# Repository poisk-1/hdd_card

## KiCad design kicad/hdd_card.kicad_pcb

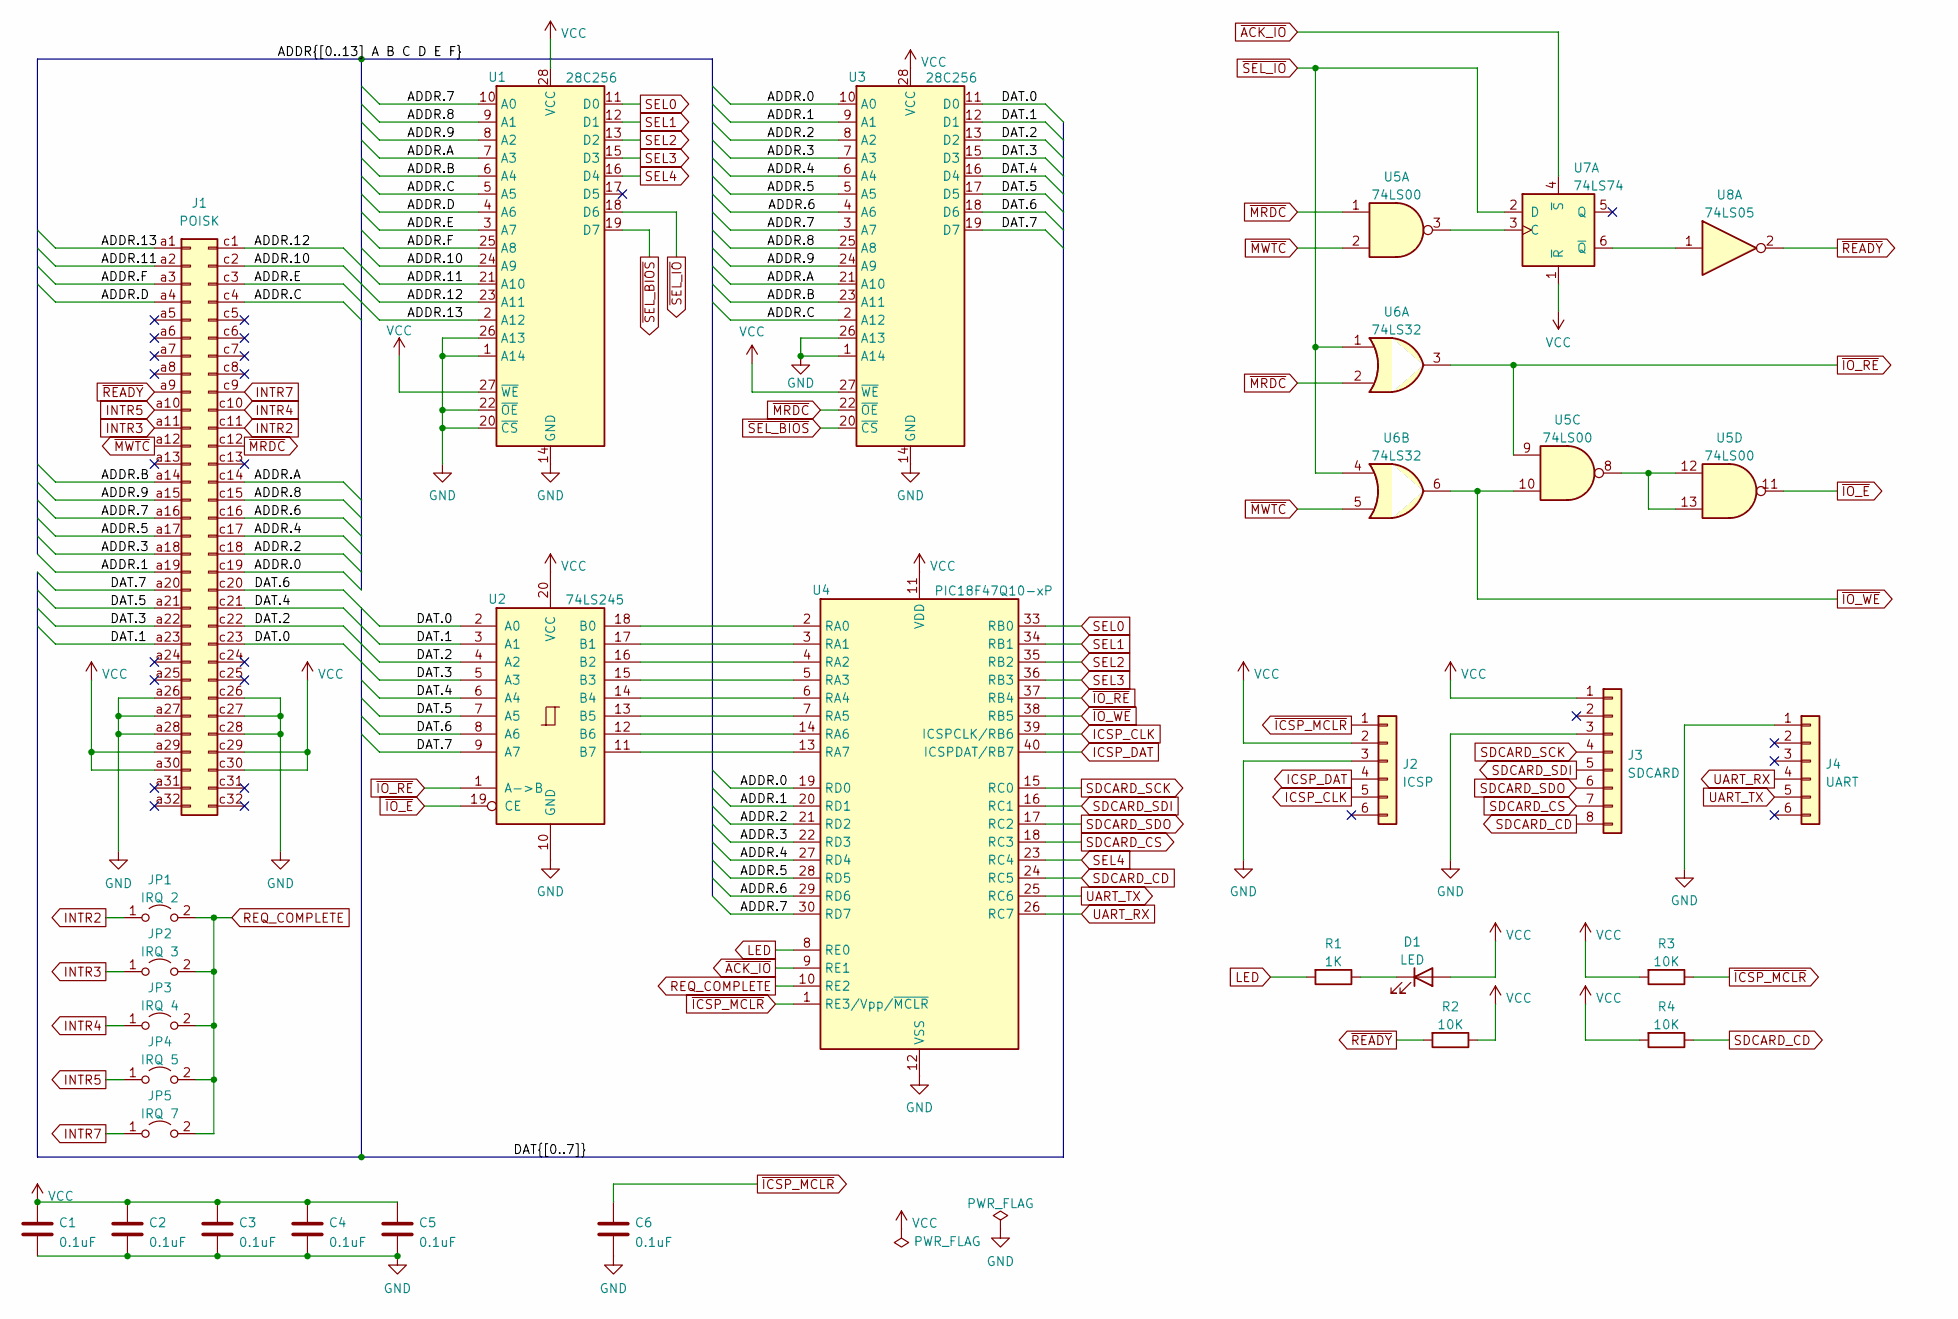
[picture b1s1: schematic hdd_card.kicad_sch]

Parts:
C1, C2, C3, C4, C5, C6: 0.1uF; C_Disc_D3.0mm_W1.6mm_P2.50mm
D1: LED; LED_D5.0mm
J1: POISK; DIN41612_R_2x32_Male_Horizontal_THT
J2: ICSP; PinHeader_1x06_P2.54mm_Vertical
J3: SDCARD; PinHeader_1x08_P2.54mm_Vertical
J4: UART; PinHeader_1x06_P2.54mm_Vertical
JP1: IRQ 2; PinHeader_1x02_P2.54mm_Vertical
JP2: IRQ 3; PinHeader_1x02_P2.54mm_Vertical
JP3: IRQ 4; PinHeader_1x02_P2.54mm_Vertical
JP4: IRQ 5; PinHeader_1x02_P2.54mm_Vertical
JP5: IRQ 7; PinHeader_1x02_P2.54mm_Vertical
R1: 1K; R_Axial_DIN0207_L6.3mm_D2.5mm_P7.62mm_Horizontal
R2, R3, R4: 10K; R_Axial_DIN0207_L6.3mm_D2.5mm_P7.62mm_Horizontal
U1, U3: 28C256; DIP-28_W15.24mm
U2: 74LS245; DIP-20_W7.62mm
U4: PIC18F47Q10-xP; DIP-40_W15.24mm
U5: 74LS00; DIP-14_W7.62mm
U6: 74LS32; DIP-14_W7.62mm
U7: 74LS74; DIP-14_W7.62mm
U8: 74LS05; DIP-14_W7.62mm

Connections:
/ADDR.0: J1.c19, U3.10 (A0), U4.19 (RD0)
/ADDR.1: J1.a19, U3.9 (A1), U4.20 (RD1)
/ADDR.2: J1.c18, U3.8 (A2), U4.21 (RD2)
/ADDR.3: J1.a18, U3.7 (A3), U4.22 (RD3)
/ADDR.4: J1.c17, U3.6 (A4), U4.27 (RD4)
/ADDR.5: J1.a17, U3.5 (A5), U4.28 (RD5)
/ADDR.6: J1.c16, U3.4 (A6), U4.29 (RD6)
/ADDR.7: J1.a16, U1.10 (A0), U3.3 (A7), U4.30 (RD7)
/ADDR.8: J1.c15, U1.9 (A1), U3.25 (A8)
/ADDR.9: J1.a15, U1.8 (A2), U3.24 (A9)
/ADDR.10: J1.c2, U1.24 (A9)
/ADDR.11: J1.a2, U1.21 (A10)
/ADDR.12: J1.c1, U1.23 (A11)
/ADDR.13: J1.a1, U1.2 (A12)
/ADDR.A: J1.c14, U1.7 (A3), U3.21 (A10)
/ADDR.B: J1.a14, U1.6 (A4), U3.23 (A11)
/ADDR.C: J1.c4, U1.5 (A5), U3.2 (A12)
/ADDR.D: J1.a4, U1.4 (A6)
/ADDR.E: J1.c3, U1.3 (A7)
/ADDR.F: J1.a3, U1.25 (A8)
/DAT.0: J1.c23, U2.2 (A0), U3.11 (D0)
/DAT.1: J1.a23, U2.3 (A1), U3.12 (D1)
/DAT.2: J1.c22, U2.4 (A2), U3.13 (D2)
/DAT.3: J1.a22, U2.5 (A3), U3.15 (D3)
/DAT.4: J1.c21, U2.6 (A4), U3.16 (D4)
/DAT.5: J1.a21, U2.7 (A5), U3.17 (D5)
/DAT.6: J1.c20, U2.8 (A6), U3.18 (D6)
/DAT.7: J1.a20, U2.9 (A7), U3.19 (D7)
GND: C1.2, C2.2, C3.2, C4.2, C5.2, C6.2, J1.a26, J1.a27, J1.a28, J1.c26, J1.c27, J1.c28, J2.3, J3.3, J4.1, U1.1 (A14), U1.14 (GND), U1.20 (~CS), U1.22 (~OE), U1.26 (A13), U2.10 (GND), U3.1 (A14), U3.14 (GND), U3.26 (A13), U4.12 (VSS), U4.31 (VSS)
ICSP_CLK: J2.5, U4.39 (ICSPCLK/RB6)
ICSP_DAT: J2.4, U4.40 (ICSPDAT/RB7)
INTR2: J1.c11, JP1.1 (A)
INTR3: J1.a11, JP2.1 (A)
INTR4: J1.c10, JP3.1 (A)
INTR5: J1.a10, JP4.1 (A)
INTR7: J1.c9, JP5.1 (A)
LED: R1.2, U4.8 (RE0)
unnamed: D1.1 (K), R1.1
unnamed: U2.11 (B7), U4.13 (RA7)
unnamed: U2.12 (B6), U4.14 (RA6)
unnamed: U2.13 (B5), U4.7 (RA5)
unnamed: U2.14 (B4), U4.6 (RA4)
unnamed: U2.15 (B3), U4.5 (RA3)
unnamed: U2.16 (B2), U4.4 (RA2)
unnamed: U2.17 (B1), U4.3 (RA1)
unnamed: U2.18 (B0), U4.2 (RA0)
unnamed: U5.3, U7.3 (C)
unnamed: U5.8, U5.12, U5.13
unnamed: U7.6 (~Q), U8.1
REQ_COMPLETE: JP1.2 (B), JP2.2 (B), JP3.2 (B), JP4.2 (B), JP5.2 (B), U4.10 (RE2)
SDCARD_CS: J3.7, U4.18 (RC3)
SDCARD_SCK: J3.4, U4.15 (RC0)
SDCARD_SDI: J3.5, U4.16 (RC1)
SDCARD_SDO: J3.6, U4.17 (RC2)
SEL0: U1.11 (D0), U4.33 (RB0)
SEL1: U1.12 (D1), U4.34 (RB1)
SEL2: U1.13 (D2), U4.35 (RB2)
SEL3: U1.15 (D3), U4.36 (RB3)
UART_RX: J4.4, U4.26 (RC7)
UART_TX: J4.5, U4.25 (RC6)
VCC: C1.1, C2.1, C3.1, C4.1, C5.1, D1.2 (A), J1.a29, J1.a30, J1.c29, J1.c30, J2.2, J3.1, R2.1, R3.2, R4.2, U1.27 (~WE), U1.28 (VCC), U2.20 (VCC), U3.27 (~WE), U3.28 (VCC), U4.11 (VDD), U4.32 (VDD), U7.1 (~R)
~ACK_IO: U4.9 (RE1), U7.4 (~S)
~ICSP_MCLR: C6.1, J2.1, R3.1, U4.1 (RE3/Vpp/~MCLR)
~IO_E: U2.19 (CE), U5.11
~IO_RE: U2.1 (A->B), U4.37 (RB4), U5.9, U6.3
~IO_WE: U4.38 (RB5), U5.10, U6.6
~MRDC: J1.c12, U3.22 (~OE), U5.1, U6.2
~MWTC: J1.a12, U5.2, U6.5
~READY: J1.a9, R2.2, U8.2
~SEL_BIOS: U1.19 (D7), U3.20 (~CS)
~SEL_IO: U1.18 (D6), U6.1, U6.4, U7.2 (D)

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
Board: 2 copper layers, 28 parts (0 on the bottom side), 72 nets, no tracks yet.

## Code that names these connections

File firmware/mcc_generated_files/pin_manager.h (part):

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// get/set ADDR_0 aliases
#define ADDR_0_TRIS                 TRISAbits.TRISA0
#define ADDR_0_LAT                  LATAbits.LATA0
#define ADDR_0_PORT                 PORTAbits.RA0
#define ADDR_0_WPU                  WPUAbits.WPUA0
#define ADDR_0_OD                   ODCONAbits.ODCA0
#define ADDR_0_ANS                  ANSELAbits.ANSELA0
#define ADDR_0_SetHigh()            do { LATAbits.LATA0 = 1; } while(0)
#define ADDR_0_SetLow()             do { LATAbits.LATA0 = 0; } while(0)
#define ADDR_0_Toggle()             do { LATAbits.LATA0 = ~LATAbits.LATA0; } while(0)
#define ADDR_0_GetValue()           PORTAbits.RA0
#define ADDR_0_SetDigitalInput()    do { TRISAbits.TRISA0 = 1; } while(0)
#define ADDR_0_SetDigitalOutput()   do { TRISAbits.TRISA0 = 0; } while(0)
#define ADDR_0_SetPullup()          do { WPUAbits.WPUA0 = 1; } while(0)
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// get/set ADDR_1 aliases
#define ADDR_1_TRIS                 TRISAbits.TRISA1
#define ADDR_1_LAT                  LATAbits.LATA1
#define ADDR_1_PORT                 PORTAbits.RA1
#define ADDR_1_WPU                  WPUAbits.WPUA1
#define ADDR_1_OD                   ODCONAbits.ODCA1
#define ADDR_1_ANS                  ANSELAbits.ANSELA1
#define ADDR_1_SetHigh()            do { LATAbits.LATA1 = 1; } while(0)
#define ADDR_1_SetLow()             do { LATAbits.LATA1 = 0; } while(0)
#define ADDR_1_Toggle()             do { LATAbits.LATA1 = ~LATAbits.LATA1; } while(0)
#define ADDR_1_GetValue()           PORTAbits.RA1
#define ADDR_1_SetDigitalInput()    do { TRISAbits.TRISA1 = 1; } while(0)
#define ADDR_1_SetDigitalOutput()   do { TRISAbits.TRISA1 = 0; } while(0)
#define ADDR_1_SetPullup()          do { WPUAbits.WPUA1 = 1; } while(0)
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// get/set ADDR_2 aliases
#define ADDR_2_TRIS                 TRISAbits.TRISA2
#define ADDR_2_LAT                  LATAbits.LATA2
#define ADDR_2_PORT                 PORTAbits.RA2
#define ADDR_2_WPU                  WPUAbits.WPUA2
#define ADDR_2_OD                   ODCONAbits.ODCA2
#define ADDR_2_ANS                  ANSELAbits.ANSELA2
#define ADDR_2_SetHigh()            do { LATAbits.LATA2 = 1; } while(0)
#define ADDR_2_SetLow()             do { LATAbits.LATA2 = 0; } while(0)
#define ADDR_2_Toggle()             do { LATAbits.LATA2 = ~LATAbits.LATA2; } while(0)
#define ADDR_2_GetValue()           PORTAbits.RA2
#define ADDR_2_SetDigitalInput()    do { TRISAbits.TRISA2 = 1; } while(0)
#define ADDR_2_SetDigitalOutput()   do { TRISAbits.TRISA2 = 0; } while(0)
#define ADDR_2_SetPullup()          do { WPUAbits.WPUA2 = 1; } while(0)
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// get/set ADDR_3 aliases
#define ADDR_3_TRIS                 TRISAbits.TRISA3
#define ADDR_3_LAT                  LATAbits.LATA3
#define ADDR_3_PORT                 PORTAbits.RA3
#define ADDR_3_WPU                  WPUAbits.WPUA3
#define ADDR_3_OD                   ODCONAbits.ODCA3
#define ADDR_3_ANS                  ANSELAbits.ANSELA3
#define ADDR_3_SetHigh()            do { LATAbits.LATA3 = 1; } while(0)
#define ADDR_3_SetLow()             do { LATAbits.LATA3 = 0; } while(0)
#define ADDR_3_Toggle()             do { LATAbits.LATA3 = ~LATAbits.LATA3; } while(0)
#define ADDR_3_GetValue()           PORTAbits.RA3
#define ADDR_3_SetDigitalInput()    do { TRISAbits.TRISA3 = 1; } while(0)
#define ADDR_3_SetDigitalOutput()   do { TRISAbits.TRISA3 = 0; } while(0)
#define ADDR_3_SetPullup()          do { WPUAbits.WPUA3 = 1; } while(0)
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// get/set ADDR_4 aliases
#define ADDR_4_TRIS                 TRISAbits.TRISA4
#define ADDR_4_LAT                  LATAbits.LATA4
#define ADDR_4_PORT                 PORTAbits.RA4
#define ADDR_4_WPU                  WPUAbits.WPUA4
#define ADDR_4_OD                   ODCONAbits.ODCA4
#define ADDR_4_ANS                  ANSELAbits.ANSELA4
#define ADDR_4_SetHigh()            do { LATAbits.LATA4 = 1; } while(0)
#define ADDR_4_SetLow()             do { LATAbits.LATA4 = 0; } while(0)
#define ADDR_4_Toggle()             do { LATAbits.LATA4 = ~LATAbits.LATA4; } while(0)
#define ADDR_4_GetValue()           PORTAbits.RA4
#define ADDR_4_SetDigitalInput()    do { TRISAbits.TRISA4 = 1; } while(0)
#define ADDR_4_SetDigitalOutput()   do { TRISAbits.TRISA4 = 0; } while(0)
#define ADDR_4_SetPullup()          do { WPUAbits.WPUA4 = 1; } while(0)
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// get/set ADDR_5 aliases
#define ADDR_5_TRIS                 TRISAbits.TRISA5
#define ADDR_5_LAT                  LATAbits.LATA5
#define ADDR_5_PORT                 PORTAbits.RA5
#define ADDR_5_WPU                  WPUAbits.WPUA5
#define ADDR_5_OD                   ODCONAbits.ODCA5
#define ADDR_5_ANS                  ANSELAbits.ANSELA5
#define ADDR_5_SetHigh()            do { LATAbits.LATA5 = 1; } while(0)
#define ADDR_5_SetLow()             do { LATAbits.LATA5 = 0; } while(0)
#define ADDR_5_Toggle()             do { LATAbits.LATA5 = ~LATAbits.LATA5; } while(0)
#define ADDR_5_GetValue()           PORTAbits.RA5
#define ADDR_5_SetDigitalInput()    do { TRISAbits.TRISA5 = 1; } while(0)
#define ADDR_5_SetDigitalOutput()   do { TRISAbits.TRISA5 = 0; } while(0)
#define ADDR_5_SetPullup()          do { WPUAbits.WPUA5 = 1; } while(0)
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// get/set ADDR_6 aliases
#define ADDR_6_TRIS                 TRISAbits.TRISA6
#define ADDR_6_LAT                  LATAbits.LATA6
#define ADDR_6_PORT                 PORTAbits.RA6
#define ADDR_6_WPU                  WPUAbits.WPUA6
#define ADDR_6_OD                   ODCONAbits.ODCA6
#define ADDR_6_ANS                  ANSELAbits.ANSELA6
#define ADDR_6_SetHigh()            do { LATAbits.LATA6 = 1; } while(0)
#define ADDR_6_SetLow()             do { LATAbits.LATA6 = 0; } while(0)
#define ADDR_6_Toggle()             do { LATAbits.LATA6 = ~LATAbits.LATA6; } while(0)
#define ADDR_6_GetValue()           PORTAbits.RA6
#define ADDR_6_SetDigitalInput()    do { TRISAbits.TRISA6 = 1; } while(0)
#define ADDR_6_SetDigitalOutput()   do { TRISAbits.TRISA6 = 0; } while(0)
#define ADDR_6_SetPullup()          do { WPUAbits.WPUA6 = 1; } while(0)
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// get/set ADDR_7 aliases
#define ADDR_7_TRIS                 TRISAbits.TRISA7
#define ADDR_7_LAT                  LATAbits.LATA7
#define ADDR_7_PORT                 PORTAbits.RA7
#define ADDR_7_WPU                  WPUAbits.WPUA7
#define ADDR_7_OD                   ODCONAbits.ODCA7
#define ADDR_7_ANS                  ANSELAbits.ANSELA7
#define ADDR_7_SetHigh()            do { LATAbits.LATA7 = 1; } while(0)
#define ADDR_7_SetLow()             do { LATAbits.LATA7 = 0; } while(0)
#define ADDR_7_Toggle()             do { LATAbits.LATA7 = ~LATAbits.LATA7; } while(0)
#define ADDR_7_GetValue()           PORTAbits.RA7
#define ADDR_7_SetDigitalInput()    do { TRISAbits.TRISA7 = 1; } while(0)
#define ADDR_7_SetDigitalOutput()   do { TRISAbits.TRISA7 = 0; } while(0)
#define ADDR_7_SetPullup()          do { WPUAbits.WPUA7 = 1; } while(0)
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// get/set SEL0 aliases
#define SEL0_TRIS                 TRISBbits.TRISB0
#define SEL0_LAT                  LATBbits.LATB0
#define SEL0_PORT                 PORTBbits.RB0
#define SEL0_WPU                  WPUBbits.WPUB0
#define SEL0_OD                   ODCONBbits.ODCB0
#define SEL0_ANS                  ANSELBbits.ANSELB0
#define SEL0_SetHigh()            do { LATBbits.LATB0 = 1; } while(0)
#define SEL0_SetLow()             do { LATBbits.LATB0 = 0; } while(0)
#define SEL0_Toggle()             do { LATBbits.LATB0 = ~LATBbits.LATB0; } while(0)
#define SEL0_GetValue()           PORTBbits.RB0
#define SEL0_SetDigitalInput()    do { TRISBbits.TRISB0 = 1; } while(0)
#define SEL0_SetDigitalOutput()   do { TRISBbits.TRISB0 = 0; } while(0)
#define SEL0_SetPullup()          do { WPUBbits.WPUB0 = 1; } while(0)
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// get/set SEL1 aliases
#define SEL1_TRIS                 TRISBbits.TRISB1
#define SEL1_LAT                  LATBbits.LATB1
#define SEL1_PORT                 PORTBbits.RB1
#define SEL1_WPU                  WPUBbits.WPUB1
#define SEL1_OD                   ODCONBbits.ODCB1
#define SEL1_ANS                  ANSELBbits.ANSELB1
#define SEL1_SetHigh()            do { LATBbits.LATB1 = 1; } while(0)
#define SEL1_SetLow()             do { LATBbits.LATB1 = 0; } while(0)
#define SEL1_Toggle()             do { LATBbits.LATB1 = ~LATBbits.LATB1; } while(0)
#define SEL1_GetValue()           PORTBbits.RB1
#define SEL1_SetDigitalInput()    do { TRISBbits.TRISB1 = 1; } while(0)
#define SEL1_SetDigitalOutput()   do { TRISBbits.TRISB1 = 0; } while(0)
#define SEL1_SetPullup()          do { WPUBbits.WPUB1 = 1; } while(0)
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// get/set SEL2 aliases
#define SEL2_TRIS                 TRISBbits.TRISB2
#define SEL2_LAT                  LATBbits.LATB2
#define SEL2_PORT                 PORTBbits.RB2
#define SEL2_WPU                  WPUBbits.WPUB2
#define SEL2_OD                   ODCONBbits.ODCB2
#define SEL2_ANS                  ANSELBbits.ANSELB2
#define SEL2_SetHigh()            do { LATBbits.LATB2 = 1; } while(0)
#define SEL2_SetLow()             do { LATBbits.LATB2 = 0; } while(0)
#define SEL2_Toggle()             do { LATBbits.LATB2 = ~LATBbits.LATB2; } while(0)
#define SEL2_GetValue()           PORTBbits.RB2
#define SEL2_SetDigitalInput()    do { TRISBbits.TRISB2 = 1; } while(0)
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
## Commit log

2022-11-11 Schematics
2022-11-14 BIOS
2022-11-14 Adjust schematic
2022-11-14 Firmware
2022-11-14 Activity LED
2022-11-15 Reset SD card
2022-11-15 UART pins
2022-11-15 Configure UART
2022-11-15 Run UART at 115200 bps
2022-11-16 Simplify BIOS
2022-11-19 Simplify
2022-11-20 Use local labels
2022-11-29 Host FAT file system
2022-12-03 Support writing
2022-12-03 Connect SDCARD_CD
2022-12-05 Connectors in schematic
2022-12-05 Use PICkit 4
2022-12-06 Fix SDCARD pinout
2022-12-06 Log mount/unmount
2022-12-06 4K IO aperture
2022-12-07 Configurable memory mapping to 128 byte blocks
2022-12-11 Check adapter before installing the int13h handler
2022-12-11 Scan drives
2022-12-11 Support verify function
2022-12-12 Support formatting floppies
2022-12-13 Keep image files open
2022-12-17 Support 1024 cylinders and verify CHS
2022-12-19 Fix for cross-track drive requests
2022-12-19 Custom int19h to boot from hard drive
2022-12-19 Report boot progress
2022-12-19 Constness
2022-12-20 Decode SEL_BIOS
2022-12-20 Program BIOS into AT28C64
2022-12-20 Fix 720K floppy
2022-12-20 Don't set SEL0-SEL3 for SEL_BIOS
2022-12-22 MBR mount/umount scripts
2022-12-23 Fix reset function handling
2022-12-23 Floppy INF and RO files
2022-12-23 Support 1.2M and 360K floppies
2022-12-25 Ask before booting from floppies
2022-12-25 BIOS at e0000 followed by IO at e1000
2022-12-26 Detect media change
2023-01-02 Read/write image sectors directly. Use fs.win as data buffer.
2023-01-02 Wait with delay when submitting IO
2023-01-07 Next read/write/verify and adaptive wait delay in SubmitIO
2023-01-11 Performance experiments
2023-01-12 Move TRISA change back to handle_read
2023-01-12 IRQ_DONE <-> INTR5
2023-01-18 Request complete interrupt. Multi-sector IO data.
2023-01-19 Use two-sector IO data
2023-01-20 Multisector transfer for writes. Simplify verify.
2023-01-22 PIC18F47Q83
2023-01-22 Use larger data buffer
2023-01-22 SEL4
2023-01-22 Increase CLTBL size
2023-01-22 Round IO size to 8K

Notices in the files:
firmware/mcc_generated_files/pin_manager.h:
(c) 2018 Microchip Technology Inc. and its subsidiaries.
